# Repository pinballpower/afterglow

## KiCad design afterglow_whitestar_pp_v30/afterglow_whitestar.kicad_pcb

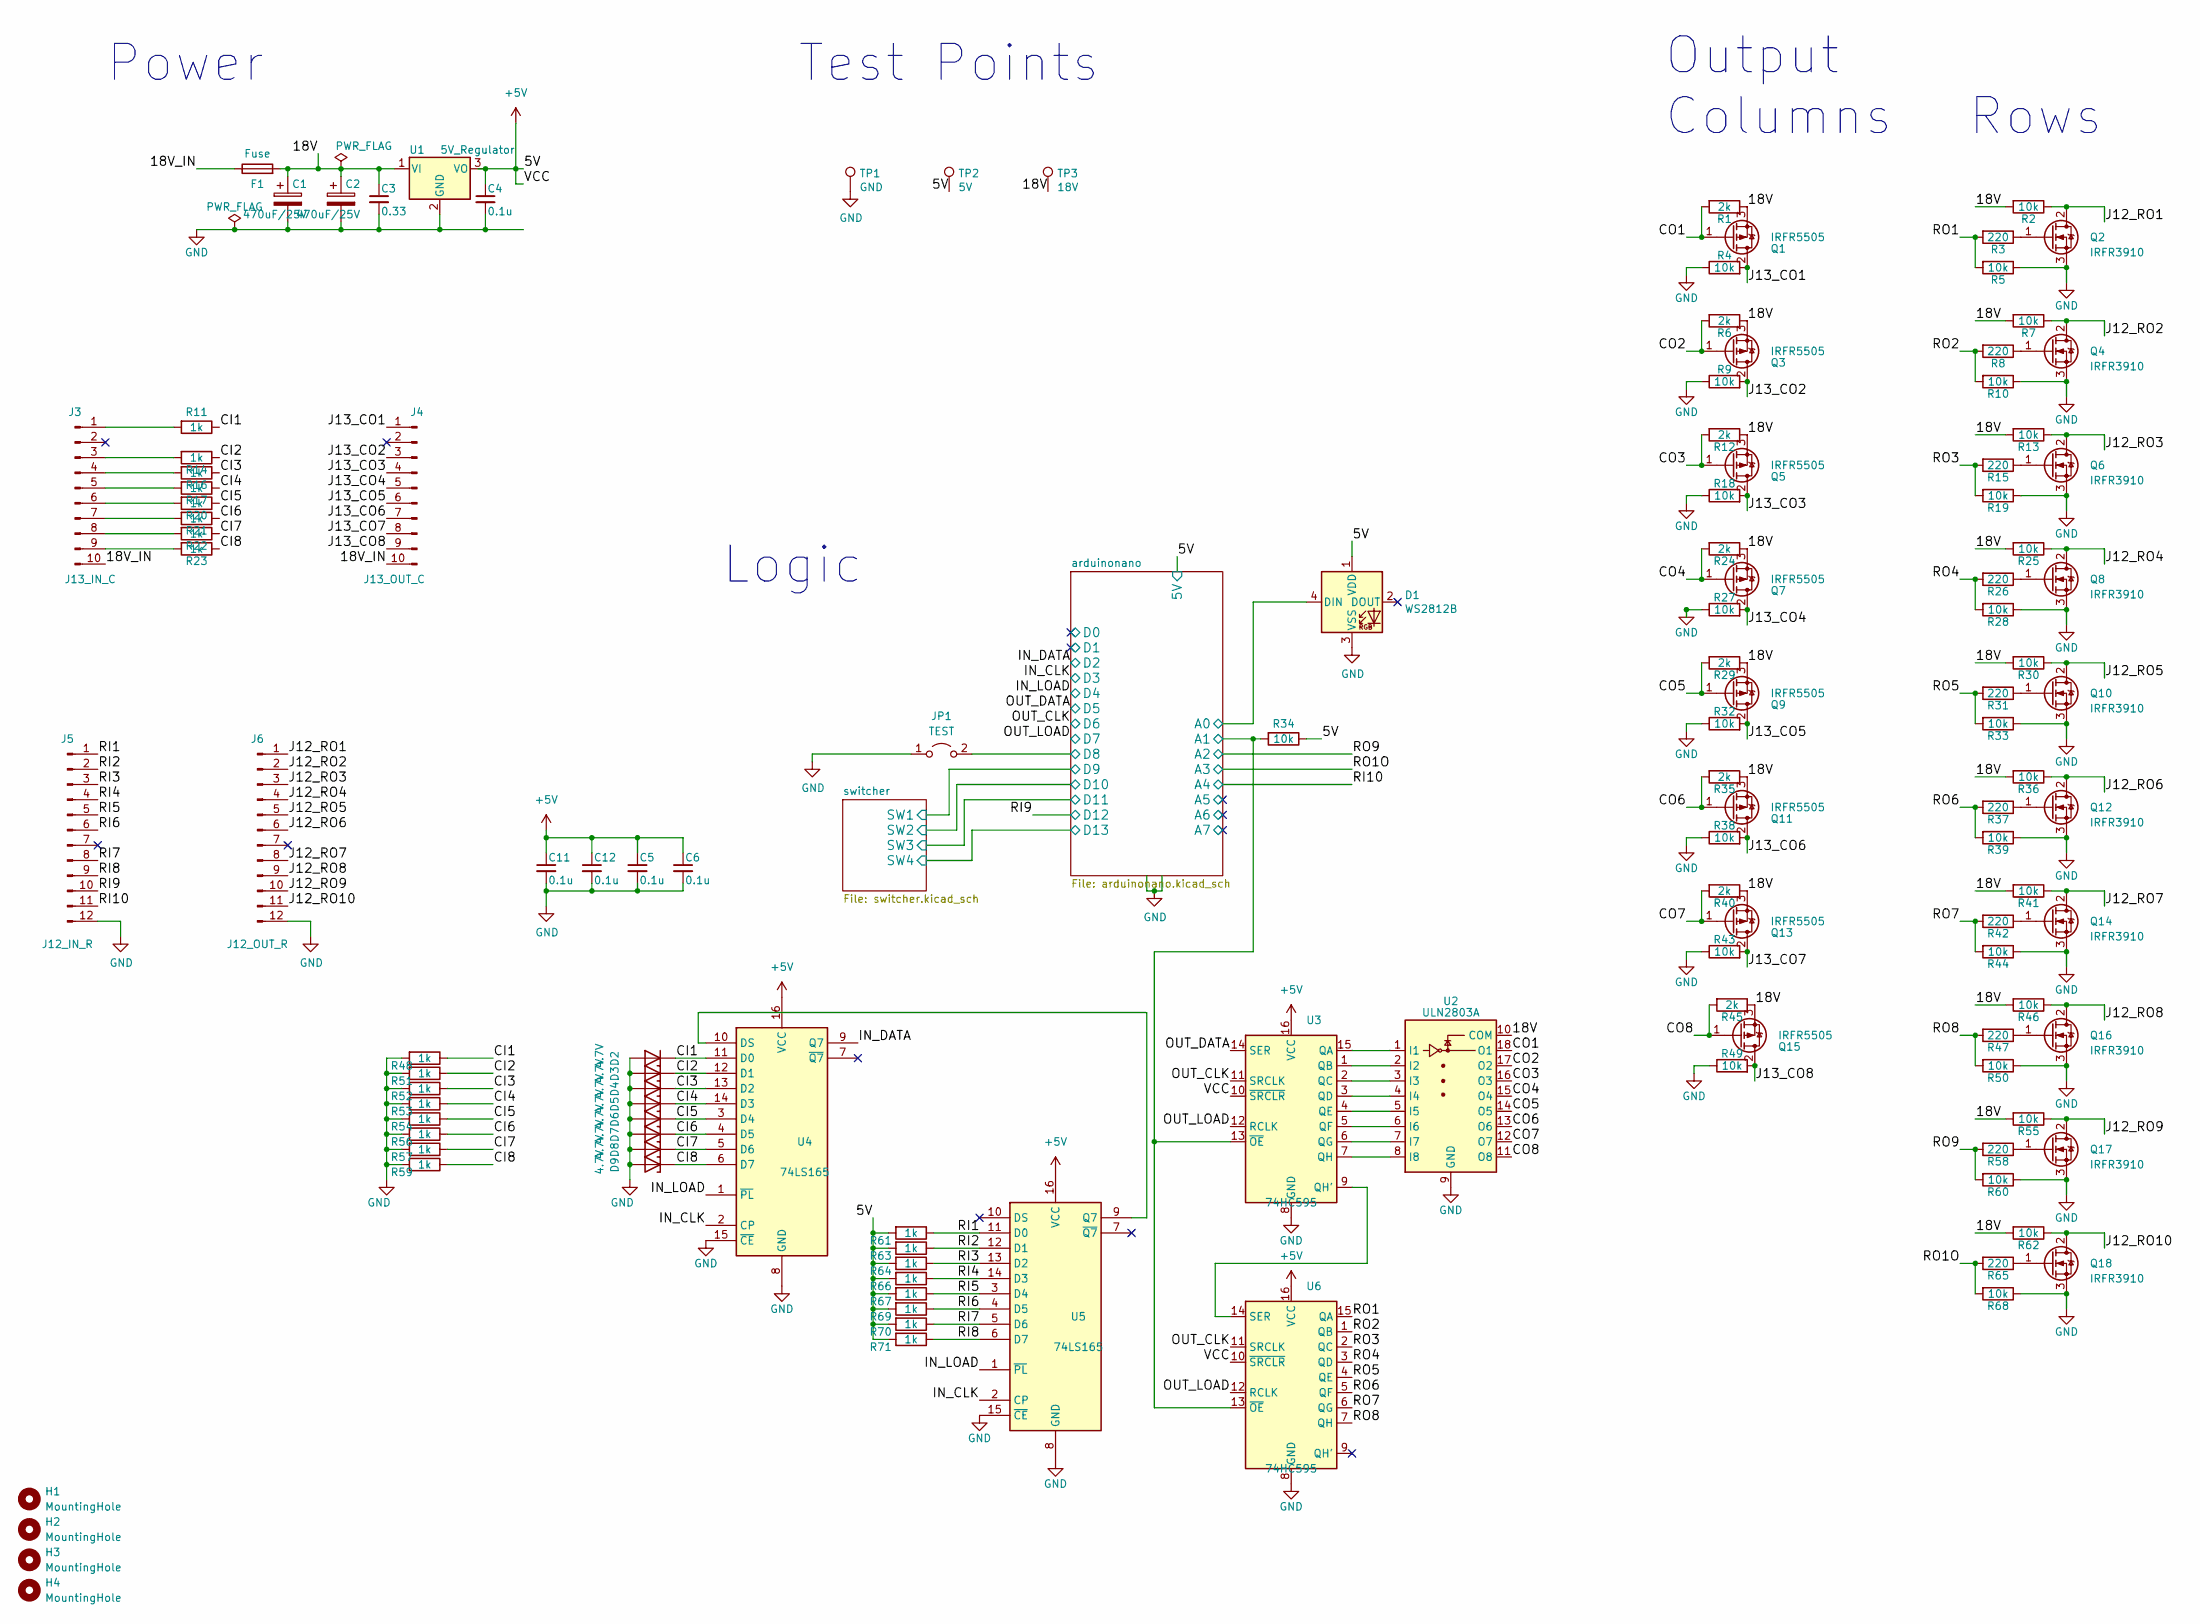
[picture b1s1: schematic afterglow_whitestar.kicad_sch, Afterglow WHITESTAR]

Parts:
C1, C2: 470uF/25V; CP_Elec_10x10.5; LCSC C402628
C3: 0.33; C_0402_1005Metric; LCSC C1740
C4, C5, C6, C11, C12: 0.1u; C_0402_1005Metric; LCSC C28233
D1: WS2812B; LED_WS2812B-PLCC4; LCSC C2761795
D2, D3, D4, D5, D6, D7, D8, D9: 4.7V; D_SOD-323_HandSoldering; LCSC C391551
F1: Fuse; Fuse_C58066_XS1033_1
H1, H2, H3, H4: MountingHole; MountingHole_4.3mm_M4
J3: J13_IN_C; Molex_KK-396_A-41791-0010_1x10_P3.96mm_Vertical
J4: J13_OUT_C; Molex_KK-396_A-41791-0010_1x10_P3.96mm_Vertical
J5: J12_IN_R; Molex_KK-396_A-41791-0012_1x12_P3.96mm_Vertical
J6: J12_OUT_R; Molex_KK-396_A-41791-0012_1x12_P3.96mm_Vertical
JP1: TEST; PinHeader_1x02_P2.54mm_Vertical
Q1, Q3, Q5, Q7, Q9, Q11, Q13, Q15: IRFR5505; TO-252-2; LCSC C26340
Q2, Q4, Q6, Q8, Q10, Q12, Q16, Q17, Q18: IRFR3910; TO-252-2; LCSC C725083
Q14: IRFR3910; TO-252-2
R1, R6, R12, R24, R29, R35, R40, R45: 2k; R_0402_1005Metric; LCSC C17604
R2, R4, R5, R7, R9, R10, R13, R18, R19, R25, R27, R28, R30, R32, R33, R36, R38, R39, R41, R43, R44, R46, R49, R50, R55, R60, R62, R68: 10k; R_0402_1005Metric; LCSC C84376
R3, R8, R15, R26, R31, R37, R42, R47, R58, R65: 220; R_0402_1005Metric; LCSC C17557
R11, R14, R16, R17, R20, R21, R22, R23, R48, R51, R52, R53, R54, R56, R57, R59, R61, R63, R64, R66, R67, R69, R70, R71: 1k; R_0402_1005Metric; LCSC C95781
R34: 10k; R_0402_1005Metric; JLCPPCB C84376
TP1: GND; PinHeader_1x01_P2.54mm_Vertical
TP2: 5V; PinHeader_1x01_P2.54mm_Vertical
TP3: 18V; PinHeader_1x01_P2.54mm_Vertical
U1: 5V_Regulator; TO-252-2; LCSC C58069
U2: ULN2803A; SOIC-18W_7.5x11.6mm_P1.27mm; LCSC C845537
U3, U6: 74HC595; SOIC-16_3.9x9.9mm_P1.27mm; LCSC C5947
U4, U5: 74LS165; SOIC-16_3.9x9.9mm_P1.27mm; LCSC C5613

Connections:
+5V: C4.1, C5.1, C6.1, C11.1, C12.1, D1.1 (VDD), R34.1, R61.2, R63.2, R64.2, R66.2, R67.2, R69.2, R70.2, R71.2, TP2.1, U1.3 (VO), U3.10 (~SRCLR), U3.16 (VCC), U4.16 (VCC), U5.16 (VCC), U6.10 (~SRCLR), U6.16 (VCC); also elsewhere on the board
/18V: C1.1, C2.1, C3.1, F1.2, Q1.3 (S), Q3.3 (S), Q5.3 (S), Q7.3 (S), Q9.3 (S), Q11.3 (S), Q13.3 (S), Q15.3 (S), R1.1, R2.2, R6.1, R7.2, R12.1, R13.2, R24.1, R25.2, R29.1, R30.2, R35.1, R36.2, R40.1, R41.2, R45.1, R46.2, R55.2, R62.2, TP3.1, U1.1 (VI), U2.10 (COM)
/18V_IN: F1.1, J3.10, J4.10
/CI1: D2.1 (K), R11.1, R48.1, U4.11 (D0)
/CI2: D3.1 (K), R14.1, R51.1, U4.12 (D1)
/CI3: D4.1 (K), R16.1, R52.1, U4.13 (D2)
/CI4: D5.1 (K), R17.1, R53.1, U4.14 (D3)
/CI5: D6.1 (K), R20.1, R54.1, U4.3 (D4)
/CI6: D7.1 (K), R21.1, R56.1, U4.4 (D5)
/CI7: D8.1 (K), R22.1, R57.1, U4.5 (D6)
/CI8: D9.1 (K), R23.1, R59.1, U4.6 (D7)
/CO1: Q1.1 (G), R1.2, U2.18 (O1)
/CO2: Q3.1 (G), R6.2, U2.17 (O2)
/CO3: Q5.1 (G), R12.2, U2.16 (O3)
/CO4: Q7.1 (G), R24.2, U2.15 (O4)
/CO5: Q9.1 (G), R29.2, U2.14 (O5)
/CO6: Q11.1 (G), R35.2, U2.13 (O6)
/CO7: Q13.1 (G), R40.2, U2.12 (O7)
/CO8: Q15.1 (G), R45.2, U2.11 (O8)
/IN_CLK: U4.2 (CP), U5.2 (CP); also elsewhere on the board
/IN_DATA: U4.9 (Q7); also elsewhere on the board
/IN_LOAD: U4.1 (~PL), U5.1 (~PL); also elsewhere on the board
/J12_RO1: J6.1, Q2.2 (D), R2.1
/J12_RO2: J6.2, Q4.2 (D), R7.1
/J12_RO3: J6.3, Q6.2 (D), R13.1
/J12_RO4: J6.4, Q8.2 (D), R25.1
/J12_RO5: J6.5, Q10.2 (D), R30.1
/J12_RO6: J6.6, Q12.2 (D), R36.1
/J12_RO7: J6.8, Q14.2 (D), R41.1
/J12_RO8: J6.9, Q16.2 (D), R46.1
/J12_RO9: J6.10, Q17.2 (D), R55.1
/J12_RO10: J6.11, Q18.2 (D), R62.1
/J13_CO1: J4.1, Q1.2 (D), R4.2
/J13_CO2: J4.3, Q3.2 (D), R9.2
/J13_CO3: J4.4, Q5.2 (D), R18.2
/J13_CO4: J4.5, Q7.2 (D), R27.2
/J13_CO5: J4.6, Q9.2 (D), R32.2
/J13_CO6: J4.7, Q11.2 (D), R38.2
/J13_CO7: J4.8, Q13.2 (D), R43.2
/J13_CO8: J4.9, Q15.2 (D), R49.2
/OUT_CLK: U3.11 (SRCLK), U6.11 (SRCLK); also elsewhere on the board
/OUT_DATA: U3.14 (SER); also elsewhere on the board
/OUT_LOAD: U3.12 (RCLK), U6.12 (RCLK); also elsewhere on the board
/RI1: J5.1, R61.1, U5.11 (D0)
/RI2: J5.2, R63.1, U5.12 (D1)
/RI3: J5.3, R64.1, U5.13 (D2)
/RI4: J5.4, R66.1, U5.14 (D3)
/RI5: J5.5, R67.1, U5.3 (D4)
/RI6: J5.6, R69.1, U5.4 (D5)
/RI7: J5.8, R70.1, U5.5 (D6)
/RI8: J5.9, R71.1, U5.6 (D7)
/RI9: J5.10; also elsewhere on the board
/RI10: J5.11; also elsewhere on the board
/RO1: R3.2, R5.2, U6.15 (QA)
/RO1O: R65.2, R68.2; also elsewhere on the board
/RO2: R8.2, R10.2, U6.1 (QB)
/RO3: R15.2, R19.2, U6.2 (QC)
/RO4: R26.2, R28.2, U6.3 (QD)
/RO5: R31.2, R33.2, U6.4 (QE)
/RO6: R37.2, R39.2, U6.5 (QF)
/RO7: R42.2, R44.2, U6.6 (QG)
/RO8: R47.2, R50.2, U6.7 (QH)
/RO9: R58.2, R60.2; also elsewhere on the board
/arduinonano/A0: D1.4 (DIN); also elsewhere on the board
/arduinonano/A1: R34.2, U3.13 (~OE), U6.13 (~OE); also elsewhere on the board
/arduinonano/D8: JP1.2 (B); also elsewhere on the board
GND: C1.2, C2.2, C3.2, C4.2, C5.2, C6.2, C11.2, C12.2, D1.3 (VSS), D2.2 (A), D3.2 (A), D4.2 (A), D5.2 (A), D6.2 (A), D7.2 (A), D8.2 (A), D9.2 (A), J5.12, J6.12, JP1.1 (A), Q2.3 (S), Q4.3 (S), Q6.3 (S), Q8.3 (S), Q10.3 (S), Q12.3 (S), Q14.3 (S), Q16.3 (S), Q17.3 (S), Q18.3 (S), R4.1, R5.1, R9.1, R10.1, R18.1, R19.1, R27.1, R28.1, R32.1, R33.1, R38.1, R39.1, R43.1, R44.1, R48.2, R49.1, R50.1, R51.2, R52.2, R53.2, R54.2, R56.2, R57.2, R59.2, R60.1, R68.1, TP1.1, U1.2 (GND), U2.9 (GND), U3.8 (GND), U4.8 (GND), U4.15 (~CE), U5.8 (GND), U5.15 (~CE), U6.8 (GND); also elsewhere on the board
unnamed: J3.1, R11.2
unnamed: J3.3, R14.2
unnamed: J3.4, R16.2
unnamed: J3.5, R17.2
unnamed: J3.6, R20.2
unnamed: J3.7, R21.2
unnamed: J3.8, R22.2
unnamed: J3.9, R23.2
unnamed: Q2.1 (G), R3.1
unnamed: Q4.1 (G), R8.1
unnamed: Q6.1 (G), R15.1
unnamed: Q8.1 (G), R26.1
unnamed: Q10.1 (G), R31.1
unnamed: Q12.1 (G), R37.1
unnamed: Q14.1 (G), R42.1
unnamed: Q16.1 (G), R47.1
unnamed: Q17.1 (G), R58.1
unnamed: Q18.1 (G), R65.1
unnamed: U2.1 (I1), U3.15 (QA)
unnamed: U2.2 (I2), U3.1 (QB)
unnamed: U2.3 (I3), U3.2 (QC)
unnamed: U2.4 (I4), U3.3 (QD)
unnamed: U2.5 (I5), U3.4 (QE)
unnamed: U2.6 (I6), U3.5 (QF)
unnamed: U2.7 (I7), U3.6 (QG)
unnamed: U2.8 (I8), U3.7 (QH)
unnamed: U3.9 (QH'), U6.14 (SER)
unnamed: U4.10 (DS), U5.9 (Q7)

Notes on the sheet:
Test Points
Power
Columns
Output
Logic
Rows

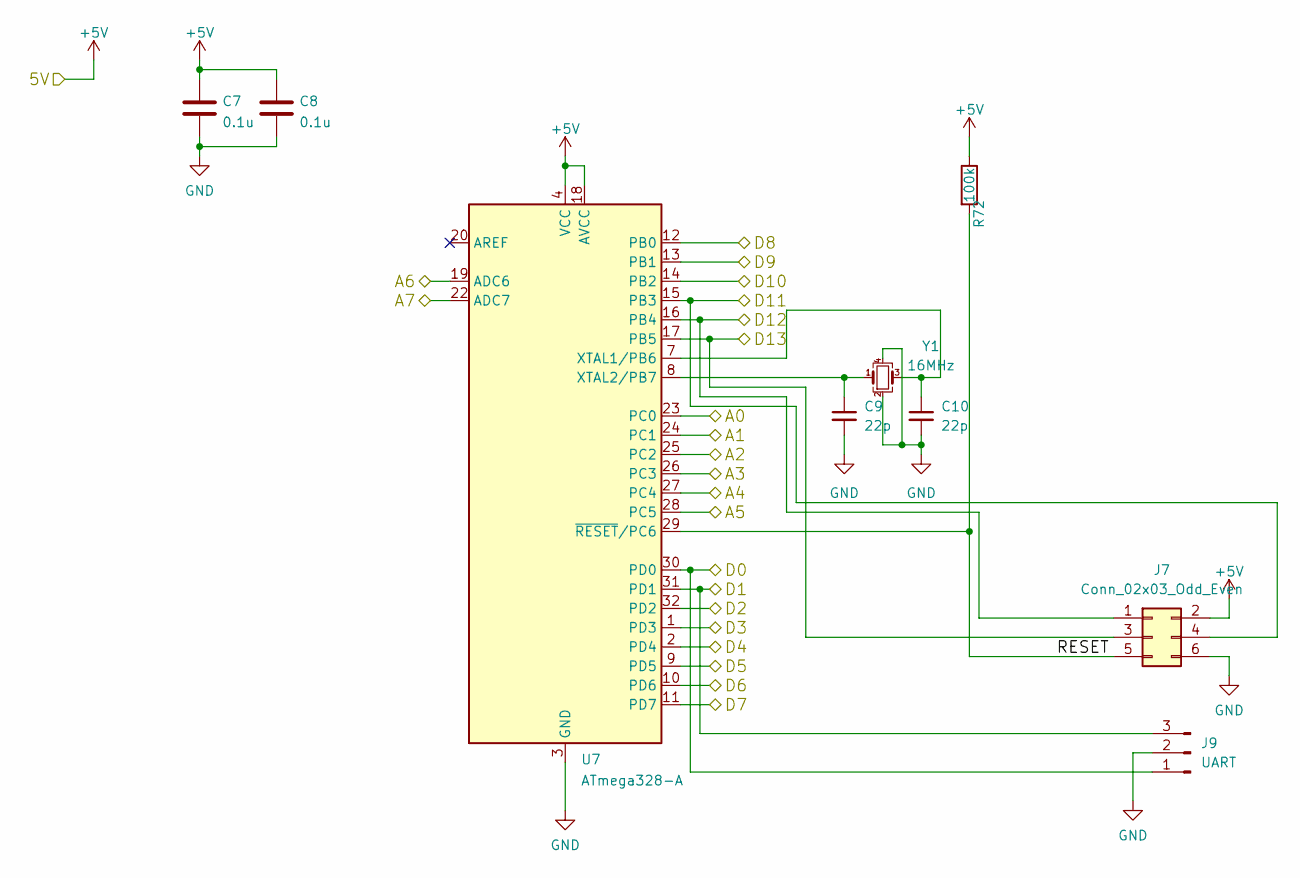
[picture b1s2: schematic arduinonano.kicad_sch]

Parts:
C7, C8: 0.1u; C_0402_1005Metric; LCSC C141382
C9, C10: 22p; C_0402_1005Metric
J7: Conn_02x03_Odd_Even; PinHeader_2x03_P2.54mm_Vertical
J9: UART; Molex_KK-254_AE-6410-03A_1x03_P2.54mm_Vertical
R72: 100k; R_0402_1005Metric; LCSC C25741
U7: ATmega328-A; TQFP-32_7x7mm_P0.8mm; LCSC C8728
Y1: 16MHz; Crystal_SMD_3225-4Pin_3.2x2.5mm

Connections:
+5V: C7.1, C8.1, J7.2, R72.1, U7.4 (VCC), U7.6 (VCC), U7.18 (AVCC); also elsewhere on the board
/IN_CLK: U7.1 (PD3); also elsewhere on the board
/IN_DATA: U7.32 (PD2); also elsewhere on the board
/IN_LOAD: U7.2 (PD4); also elsewhere on the board
/OUT_CLK: U7.10 (PD6); also elsewhere on the board
/OUT_DATA: U7.9 (PD5); also elsewhere on the board
/OUT_LOAD: U7.11 (PD7); also elsewhere on the board
/RI9: J7.1, U7.16 (PB4); also elsewhere on the board
/RI10: U7.27 (PC4); also elsewhere on the board
/RO1O: U7.26 (PC3); also elsewhere on the board
/RO9: U7.25 (PC2); also elsewhere on the board
/arduinonano/A0: U7.23 (PC0); also elsewhere on the board
/arduinonano/A1: U7.24 (PC1); also elsewhere on the board
/arduinonano/A5: U7.28 (PC5)
/arduinonano/A6: U7.19 (ADC6)
/arduinonano/A7: U7.22 (ADC7)
/arduinonano/D0: J9.1, U7.30 (PD0)
/arduinonano/D1: J9.3, U7.31 (PD1)
/arduinonano/D8: U7.12 (PB0); also elsewhere on the board
/arduinonano/D9: U7.13 (PB1); also elsewhere on the board
/arduinonano/D10: U7.14 (PB2); also elsewhere on the board
/arduinonano/D11: J7.4, U7.15 (PB3); also elsewhere on the board
/arduinonano/D13: J7.3, U7.17 (PB5); also elsewhere on the board
/arduinonano/RESET: J7.5, R72.2, U7.29 (~RESET/PC6)
GND: C7.2, C8.2, C9.2, C10.2, J7.6, J9.2, U7.3 (GND), U7.5 (GND), U7.21 (GND), Y1.2, Y1.4; also elsewhere on the board
unnamed: C9.1, U7.8 (XTAL2/PB7), Y1.1
unnamed: C10.1, U7.7 (XTAL1/PB6), Y1.3

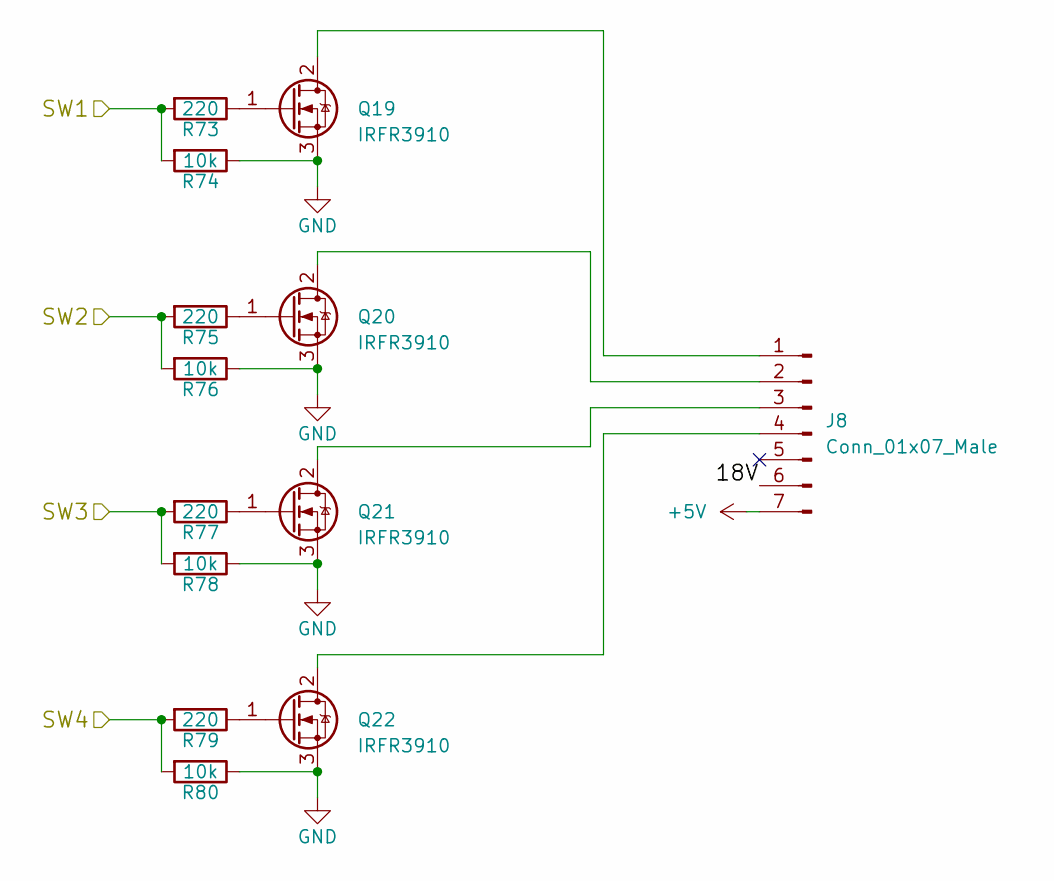
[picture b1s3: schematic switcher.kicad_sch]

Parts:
J8: Conn_01x07_Male; Molex_KK-396_A-41791-0007_1x07_P3.96mm_Vertical
Q19, Q20, Q21, Q22: IRFR3910; TO-252-2; LCSC C725083
R73, R75, R77, R79: 220; R_0402_1005Metric; LCSC C17557
R74, R76, R78, R80: 10k; R_0402_1005Metric; LCSC C84376

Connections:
+5V: J8.7; also elsewhere on the board
/arduinonano/D9: R73.2, R74.2; also elsewhere on the board
/arduinonano/D10: R75.2, R76.2; also elsewhere on the board
/arduinonano/D11: R77.2, R78.2; also elsewhere on the board
/arduinonano/D13: R79.2, R80.2; also elsewhere on the board
/switcher/18V: J8.6
GND: Q19.3 (S), Q20.3 (S), Q21.3 (S), Q22.3 (S), R74.1, R76.1, R78.1, R80.1; also elsewhere on the board
unnamed: J8.1, Q19.2 (D)
unnamed: J8.2, Q20.2 (D)
unnamed: J8.3, Q21.2 (D)
unnamed: J8.4, Q22.2 (D)
unnamed: Q19.1 (G), R73.1
unnamed: Q20.1 (G), R75.1
unnamed: Q21.1 (G), R77.1
unnamed: Q22.1 (G), R79.1

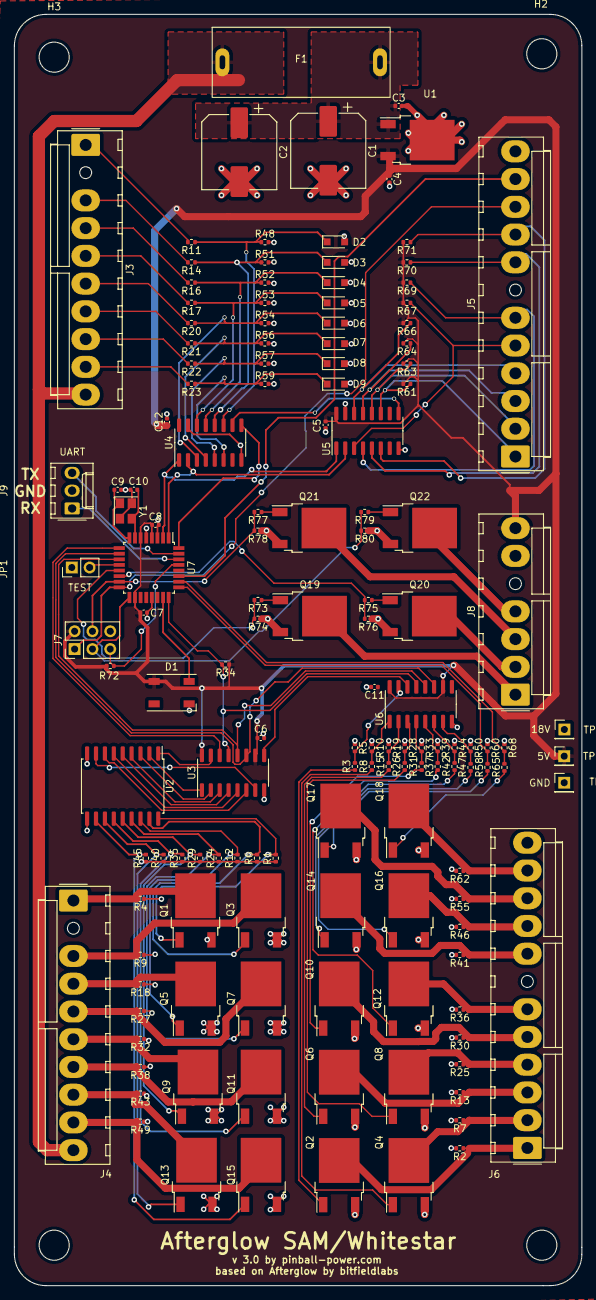
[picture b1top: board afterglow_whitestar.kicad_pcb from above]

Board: 4 copper layers, 81.0 x 181.4 mm, 147 parts (0 on the bottom side), 112 nets.

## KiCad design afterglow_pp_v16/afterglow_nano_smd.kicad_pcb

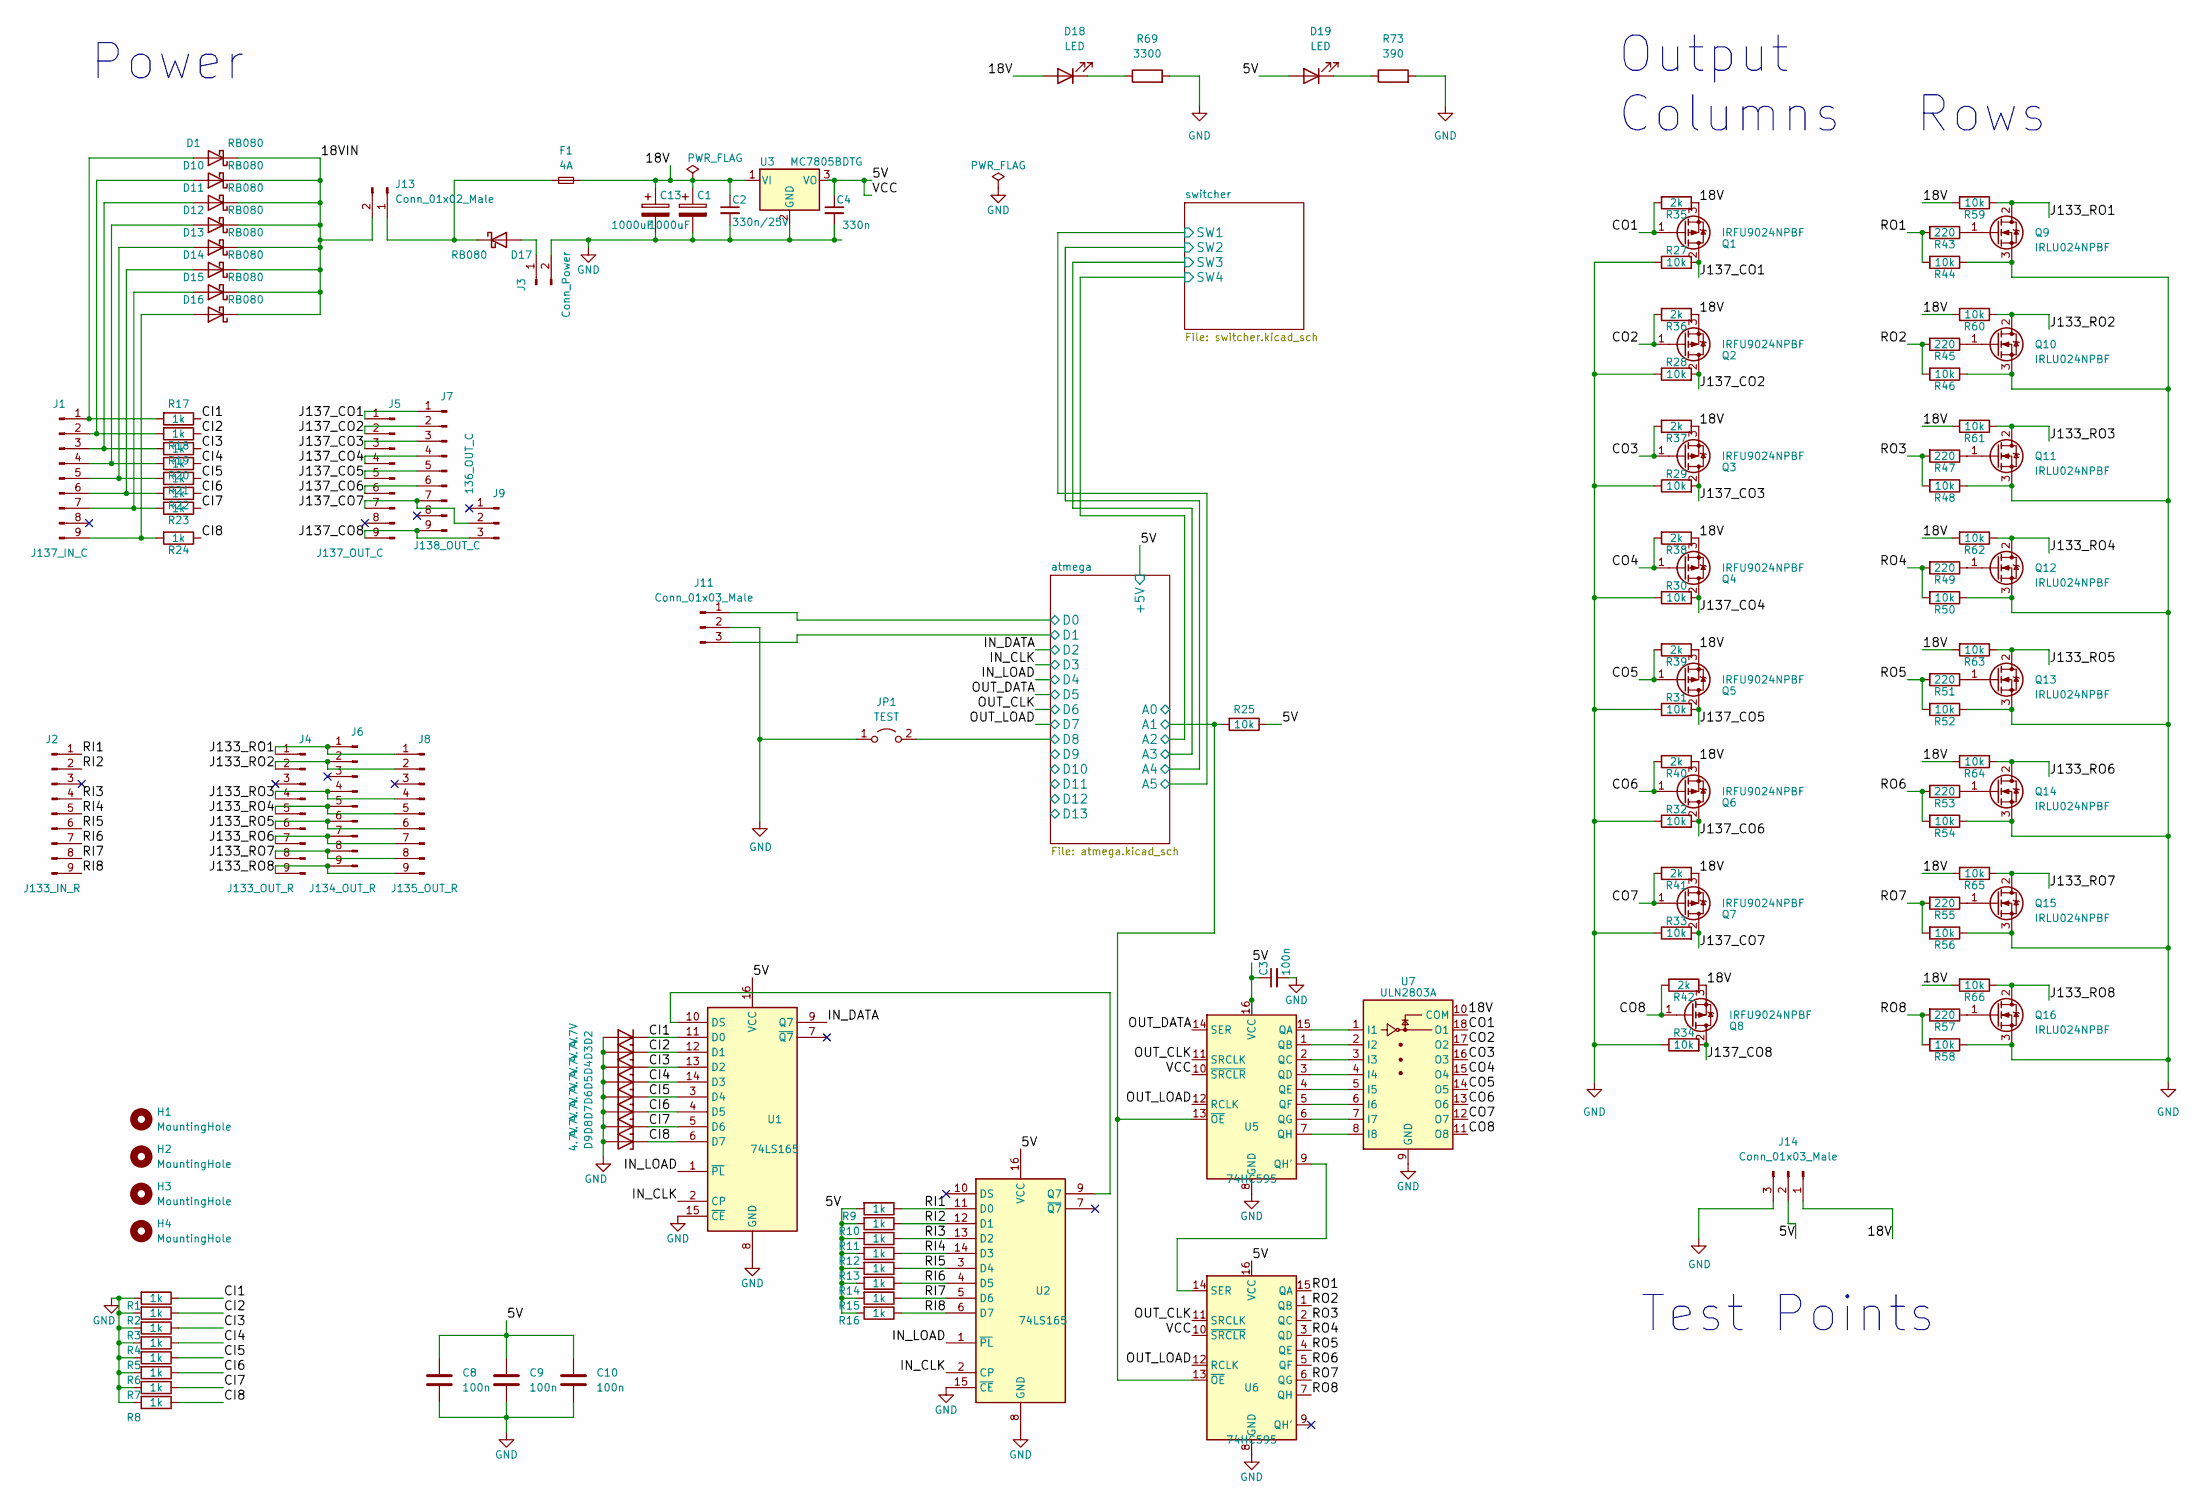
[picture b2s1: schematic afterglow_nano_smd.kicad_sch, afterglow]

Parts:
C1, C13: 1000uF; CP_Radial_D10.0mm_P5.00mm
C2: 330n/25V; C_0805_2012Metric
C3, C8, C9, C10: 100n; C_0402_1005Metric
C4: 330n; C_0805_2012Metric
D1, D10, D11, D12, D13, D14, D15, D16, D17: RB080; D_SOD-128
D2, D3, D4, D5, D6, D7, D8, D9: 4.7V; D_SOD-323
D18, D19: LED; LED_0603_1608Metric
F1: 4A; Fuse_C58066_XS1033_1
H1, H2, H3, H4: MountingHole; MountingHole_4.3mm_M4
J1: J137_IN_C; Molex_KK-41791-9_9x3.96mm_Straight
J2: J133_IN_R; Molex_KK-6410-09_09x2.54mm_Straight
J3: Conn_Power; Molex_KK-41791-02_02x3.96mm_Straight
J4: J133_OUT_R; Molex_KK-6410-09_09x2.54mm_Straight
J5: J137_OUT_C; Molex_KK-41791-9_9x3.96mm_Straight
J6: J134_OUT_R; Molex_KK-6410-09_09x2.54mm_Straight
J7: J138_OUT_C; Molex_KK-41791-9_9x3.96mm_Straight
J8: J135_OUT_R; Molex_KK-6410-09_09x2.54mm_Straight
J9: 136_OUT_C; Molex_KK-41791-03_03x3.96mm_Straight
J11: Conn_01x03_Male; Molex_KK-254_AE-6410-03A_1x03_P2.54mm_Vertical
J13: Conn_01x02_Male; PinHeader_1x02_P2.54mm_Vertical
J14: Conn_01x03_Male; PinHeader_1x03_P2.54mm_Vertical
JP1: TEST; PinHeader_1x02_P2.54mm_Vertical
Q1, Q2, Q3, Q4, Q5, Q6, Q7, Q8: IRFU9024NPBF; TO-220-3_Vertical
Q9, Q10, Q11, Q12, Q13, Q14, Q15, Q16: IRLU024NPBF; TO-220-3_Vertical
R1, R2, R3, R4, R5, R6, R7, R8, R9, R10, R11, R12, R13, R14, R15, R16, R17, R18, R19, R20, R21, R22, R23, R24: 1k; R_0402_1005Metric
R25, R27, R28, R29, R30, R31, R32, R33, R34, R44, R46, R48, R50, R52, R54, R56, R58, R59, R60, R61, R62, R63, R64, R65, R66: 10k; R_0402_1005Metric
R35, R36, R37, R38, R39, R40, R41, R42: 2k; R_0402_1005Metric
R43, R45, R47, R49, R51, R53, R55, R57: 220; R_0402_1005Metric
R69: 3300; R_0402_1005Metric
R73: 390; R_0402_1005Metric
U1, U2: 74LS165; SOIC-16_3.9x9.9mm_Pitch1.27mm
U3: MC7805BDTG; TO-252-2
U5, U6: 74HC595; SOIC-16_3.9x9.9mm_Pitch1.27mm
U7: ULN2803A; SOIC-18W_7.5x11.6mm_Pitch1.27mm

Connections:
/5V: C3.1, C4.1, C8.1, C9.1, C10.1, D19.2 (A), J14.2, R9.2, R10.2, R11.2, R12.2, R13.2, R14.2, R15.2, R16.2, R25.1, U1.16 (VCC), U2.16 (VCC), U3.3 (VO), U5.10 (~SRCLR), U5.16 (VCC), U6.10 (~SRCLR), U6.16 (VCC); also elsewhere on the board
/18V: C1.1, C2.1, C13.1, D18.2 (A), F1.2, J14.1, Q1.3 (S), Q2.3 (S), Q3.3 (S), Q4.3 (S), Q5.3 (S), Q6.3 (S), Q7.3 (S), Q8.3 (S), R35.1, R36.1, R37.1, R38.1, R39.1, R40.1, R41.1, R42.1, R59.2, R60.2, R61.2, R62.2, R63.2, R64.2, R65.2, R66.2, U3.1 (VI), U7.10 (COM)
/18VIN: D1.1 (K), D10.1 (K), D11.1 (K), D12.1 (K), D13.1 (K), D14.1 (K), D15.1 (K), D16.1 (K), J13.2
/CI1: D2.1 (K), R1.1, R17.1, U1.11 (D0)
/CI2: D3.1 (K), R2.1, R18.1, U1.12 (D1)
/CI3: D4.1 (K), R3.1, R19.1, U1.13 (D2)
/CI4: D5.1 (K), R4.1, R20.1, U1.14 (D3)
/CI5: D6.1 (K), R5.1, R21.1, U1.3 (D4)
/CI6: D7.1 (K), R6.1, R22.1, U1.4 (D5)
/CI7: D8.1 (K), R7.1, R23.1, U1.5 (D6)
/CI8: D9.1 (K), R8.1, R24.1, U1.6 (D7)
/CO1: Q1.1 (G), R35.2, U7.18 (O1)
/CO2: Q2.1 (G), R36.2, U7.17 (O2)
/CO3: Q3.1 (G), R37.2, U7.16 (O3)
/CO4: Q4.1 (G), R38.2, U7.15 (O4)
/CO5: Q5.1 (G), R39.2, U7.14 (O5)
/CO6: Q6.1 (G), R40.2, U7.13 (O6)
/CO7: Q7.1 (G), R41.2, U7.12 (O7)
/CO8: Q8.1 (G), R42.2, U7.11 (O8)
/IN_CLK: U1.2 (CP), U2.2 (CP); also elsewhere on the board
/IN_DATA: U1.9 (Q7); also elsewhere on the board
/IN_LOAD: U1.1 (~PL), U2.1 (~PL); also elsewhere on the board
/J133_RO1: J4.1, J6.1, J8.1, Q9.2 (D), R59.1
/J133_RO2: J4.2, J6.2, J8.2, Q10.2 (D), R60.1
/J133_RO3: J4.4, J6.4, J8.4, Q11.2 (D), R61.1
/J133_RO4: J4.5, J6.5, J8.5, Q12.2 (D), R62.1
/J133_RO5: J4.6, J6.6, J8.6, Q13.2 (D), R63.1
/J133_RO6: J4.7, J6.7, J8.7, Q14.2 (D), R64.1
/J133_RO7: J4.8, J6.8, J8.8, Q15.2 (D), R65.1
/J133_RO8: J4.9, J6.9, J8.9, Q16.2 (D), R66.1
/J137_CO1: J5.1, J7.1, Q1.2 (D), R27.2
/J137_CO2: J5.2, J7.2, Q2.2 (D), R28.2
/J137_CO3: J5.3, J7.3, Q3.2 (D), R29.2
/J137_CO4: J5.4, J7.4, Q4.2 (D), R30.2
/J137_CO5: J5.5, J7.5, Q5.2 (D), R31.2
/J137_CO6: J5.6, J7.6, Q6.2 (D), R32.2
/J137_CO7: J5.7, J7.7, J9.2, Q7.2 (D), R33.2
/J137_CO8: J5.9, J7.9, J9.3, Q8.2 (D), R34.2
/OUT_CLK: U5.11 (SRCLK), U6.11 (SRCLK); also elsewhere on the board
/OUT_DATA: U5.14 (SER); also elsewhere on the board
/OUT_LOAD: U5.12 (RCLK), U6.12 (RCLK); also elsewhere on the board
/RI1: J2.1, R9.1, U2.11 (D0)
/RI2: J2.2, R10.1, U2.12 (D1)
/RI3: J2.4, R11.1, U2.13 (D2)
/RI4: J2.5, R12.1, U2.14 (D3)
/RI5: J2.6, R13.1, U2.3 (D4)
/RI6: J2.7, R14.1, U2.4 (D5)
/RI7: J2.8, R15.1, U2.5 (D6)
/RI8: J2.9, R16.1, U2.6 (D7)
/RO1: R43.2, R44.2, U6.15 (QA)
/RO2: R45.2, R46.2, U6.1 (QB)
/RO3: R47.2, R48.2, U6.2 (QC)
/RO4: R49.2, R50.2, U6.3 (QD)
/RO5: R51.2, R52.2, U6.4 (QE)
/RO6: R53.2, R54.2, U6.5 (QF)
/RO7: R55.2, R56.2, U6.6 (QG)
/RO8: R57.2, R58.2, U6.7 (QH)
/atmega/A1: R25.2, U5.13 (~OE), U6.13 (~OE); also elsewhere on the board
/atmega/D0: J11.1; also elsewhere on the board
/atmega/D1: J11.3; also elsewhere on the board
/atmega/D8: JP1.2 (B); also elsewhere on the board
GND: C1.2, C2.2, C3.2, C4.2, C8.2, C9.2, C10.2, C13.2, D2.2 (A), D3.2 (A), D4.2 (A), D5.2 (A), D6.2 (A), D7.2 (A), D8.2 (A), D9.2 (A), J3.2, J11.2, J14.3, JP1.1 (A), Q9.3 (S), Q10.3 (S), Q11.3 (S), Q12.3 (S), Q13.3 (S), Q14.3 (S), Q15.3 (S), Q16.3 (S), R1.2, R2.2, R3.2, R4.2, R5.2, R6.2, R7.2, R8.2, R27.1, R28.1, R29.1, R30.1, R31.1, R32.1, R33.1, R34.1, R44.1, R46.1, R48.1, R50.1, R52.1, R54.1, R56.1, R58.1, R69.2, R73.2, U1.8 (GND), U1.15 (~CE), U2.8 (GND), U2.15 (~CE), U3.2 (GND), U5.8 (GND), U6.8 (GND), U7.9 (GND); also elsewhere on the board
unnamed: D1.2 (A), J1.1, R17.2
unnamed: D10.2 (A), J1.2, R18.2
unnamed: D11.2 (A), J1.3, R19.2
unnamed: D12.2 (A), J1.4, R20.2
unnamed: D13.2 (A), J1.5, R21.2
unnamed: D14.2 (A), J1.6, R22.2
unnamed: D15.2 (A), J1.7, R23.2
unnamed: D16.2 (A), J1.9, R24.2
unnamed: D17.1 (K), F1.1, J13.1
unnamed: D17.2 (A), J3.1
unnamed: D18.1 (K), R69.1
unnamed: D19.1 (K), R73.1
unnamed: Q9.1 (G), R43.1
unnamed: Q10.1 (G), R45.1
unnamed: Q11.1 (G), R47.1
unnamed: Q12.1 (G), R49.1
unnamed: Q13.1 (G), R51.1
unnamed: Q14.1 (G), R53.1
unnamed: Q15.1 (G), R55.1
unnamed: Q16.1 (G), R57.1
unnamed: U1.10 (DS), U2.9 (Q7)
unnamed: U5.1 (QB), U7.2 (I2)
unnamed: U5.2 (QC), U7.3 (I3)
unnamed: U5.3 (QD), U7.4 (I4)
unnamed: U5.4 (QE), U7.5 (I5)
unnamed: U5.5 (QF), U7.6 (I6)
unnamed: U5.6 (QG), U7.7 (I7)
unnamed: U5.7 (QH), U7.8 (I8)
unnamed: U5.9 (QH'), U6.14 (SER)
unnamed: U5.15 (QA), U7.1 (I1)

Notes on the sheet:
Rows
Columns
Test Points
Power
Output

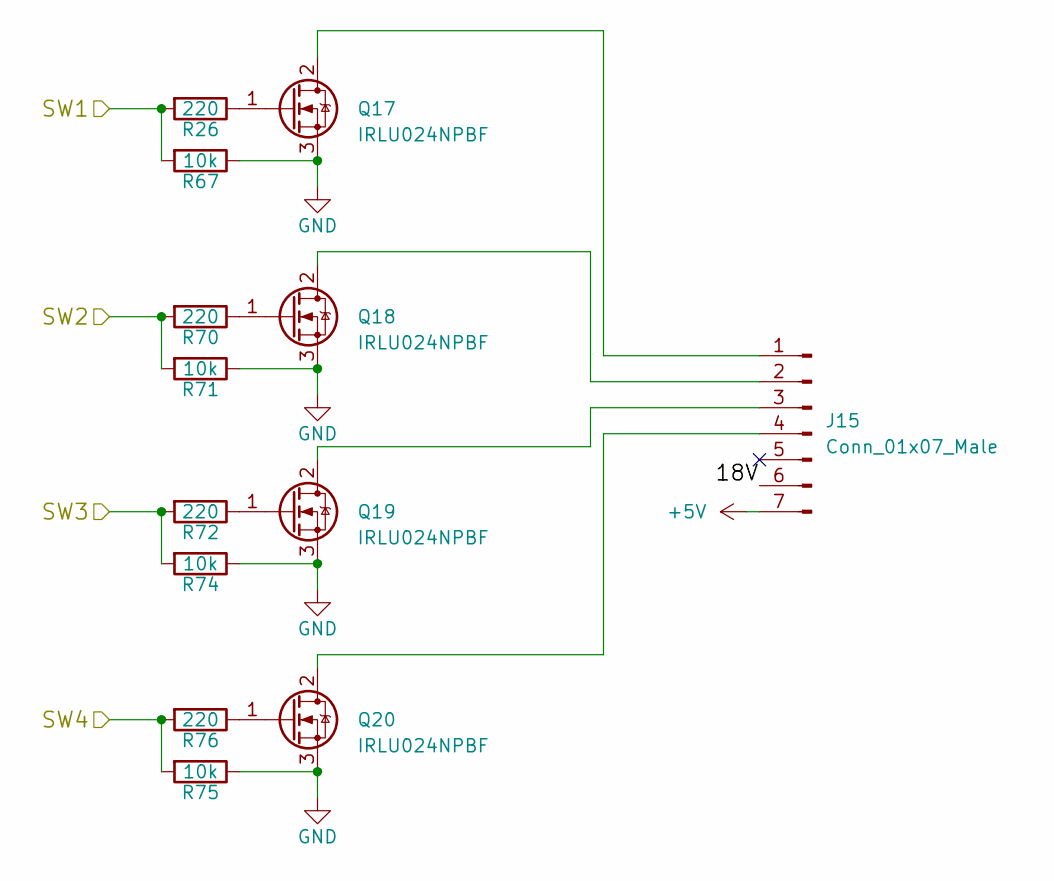
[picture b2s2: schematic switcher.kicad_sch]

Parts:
J15: Conn_01x07_Male; Molex_KK-396_A-41791-0007_1x07_P3.96mm_Vertical
Q17, Q18, Q19, Q20: IRLU024NPBF; TO-220-3_Vertical
R26, R70, R72, R76: 220; R_0402_1005Metric; LCSC C17557
R67, R71, R74, R75: 10k; R_0402_1005Metric; LCSC C84376

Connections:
+5V: J15.7
/atmega/A2: R75.2, R76.2; also elsewhere on the board
/atmega/A3: R72.2, R74.2; also elsewhere on the board
/atmega/A4: R70.2, R71.2; also elsewhere on the board
/atmega/A5: R26.2, R67.2; also elsewhere on the board
/switcher/18V: J15.6
GND: Q17.3 (S), Q18.3 (S), Q19.3 (S), Q20.3 (S), R67.1, R71.1, R74.1, R75.1; also elsewhere on the board
unnamed: J15.1, Q17.2 (D)
unnamed: J15.2, Q18.2 (D)
unnamed: J15.3, Q19.2 (D)
unnamed: J15.4, Q20.2 (D)
unnamed: Q17.1 (G), R26.1
unnamed: Q18.1 (G), R70.1
unnamed: Q19.1 (G), R72.1
unnamed: Q20.1 (G), R76.1

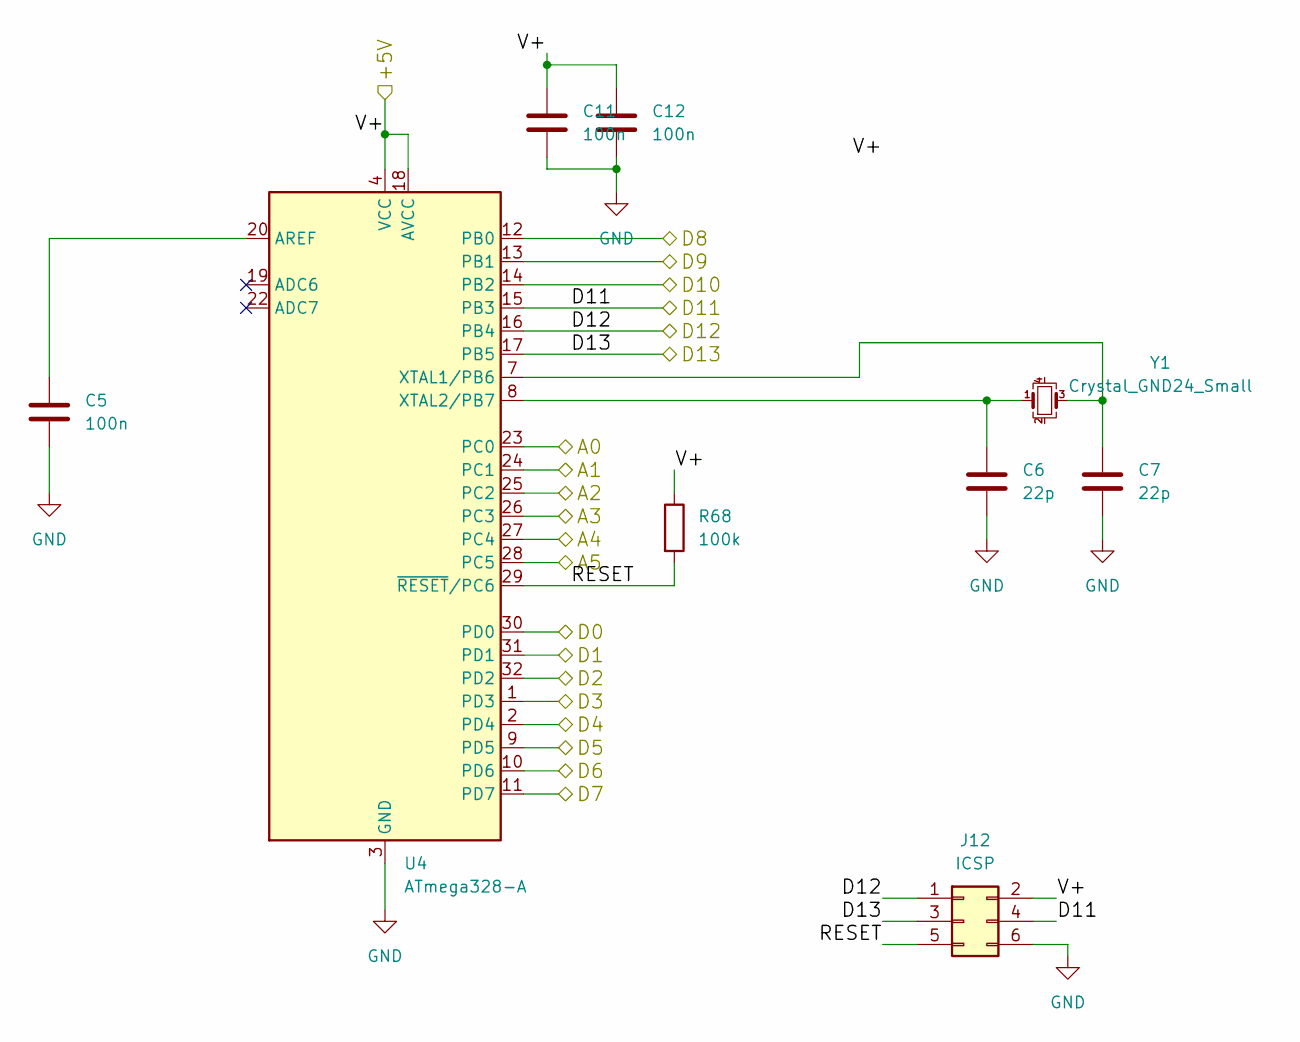
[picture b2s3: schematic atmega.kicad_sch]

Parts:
C5, C11, C12: 100n; C_0402_1005Metric
C6, C7: 22p; C_0402_1005Metric
J12: ICSP; PinHeader_2x03_P2.54mm_Vertical
R68: 100k; R_0402_1005Metric
U4: ATmega328-A; TQFP-32_7x7mm_P0.8mm
Y1: Crystal_GND24_Small; Crystal_SMD_3225-4Pin_3.2x2.5mm

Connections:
/5V: C11.1, C12.1, J12.2, R68.1, U4.4 (VCC), U4.6 (VCC), U4.18 (AVCC); also elsewhere on the board
/IN_CLK: U4.1 (PD3); also elsewhere on the board
/IN_DATA: U4.32 (PD2); also elsewhere on the board
/IN_LOAD: U4.2 (PD4); also elsewhere on the board
/OUT_CLK: U4.10 (PD6); also elsewhere on the board
/OUT_DATA: U4.9 (PD5); also elsewhere on the board
/OUT_LOAD: U4.11 (PD7); also elsewhere on the board
/atmega/A0: U4.23 (PC0)
/atmega/A1: U4.24 (PC1); also elsewhere on the board
/atmega/A2: U4.25 (PC2); also elsewhere on the board
/atmega/A3: U4.26 (PC3); also elsewhere on the board
/atmega/A4: U4.27 (PC4); also elsewhere on the board
/atmega/A5: U4.28 (PC5); also elsewhere on the board
/atmega/D0: U4.30 (PD0); also elsewhere on the board
/atmega/D1: U4.31 (PD1); also elsewhere on the board
/atmega/D8: U4.12 (PB0); also elsewhere on the board
/atmega/D9: U4.13 (PB1)
/atmega/D10: U4.14 (PB2)
/atmega/D11: J12.4, U4.15 (PB3)
/atmega/D12: J12.1, U4.16 (PB4)
/atmega/D13: J12.3, U4.17 (PB5)
/atmega/RESET: J12.5, R68.2, U4.29 (~RESET/PC6)
GND: C5.2, C6.2, C7.2, C11.2, C12.2, J12.6, U4.3 (GND), U4.5 (GND), U4.21 (GND); also elsewhere on the board
unnamed: C5.1, U4.20 (AREF)
unnamed: C6.1, U4.8 (XTAL2/PB7), Y1.1
unnamed: C7.1, U4.7 (XTAL1/PB6), Y1.3
